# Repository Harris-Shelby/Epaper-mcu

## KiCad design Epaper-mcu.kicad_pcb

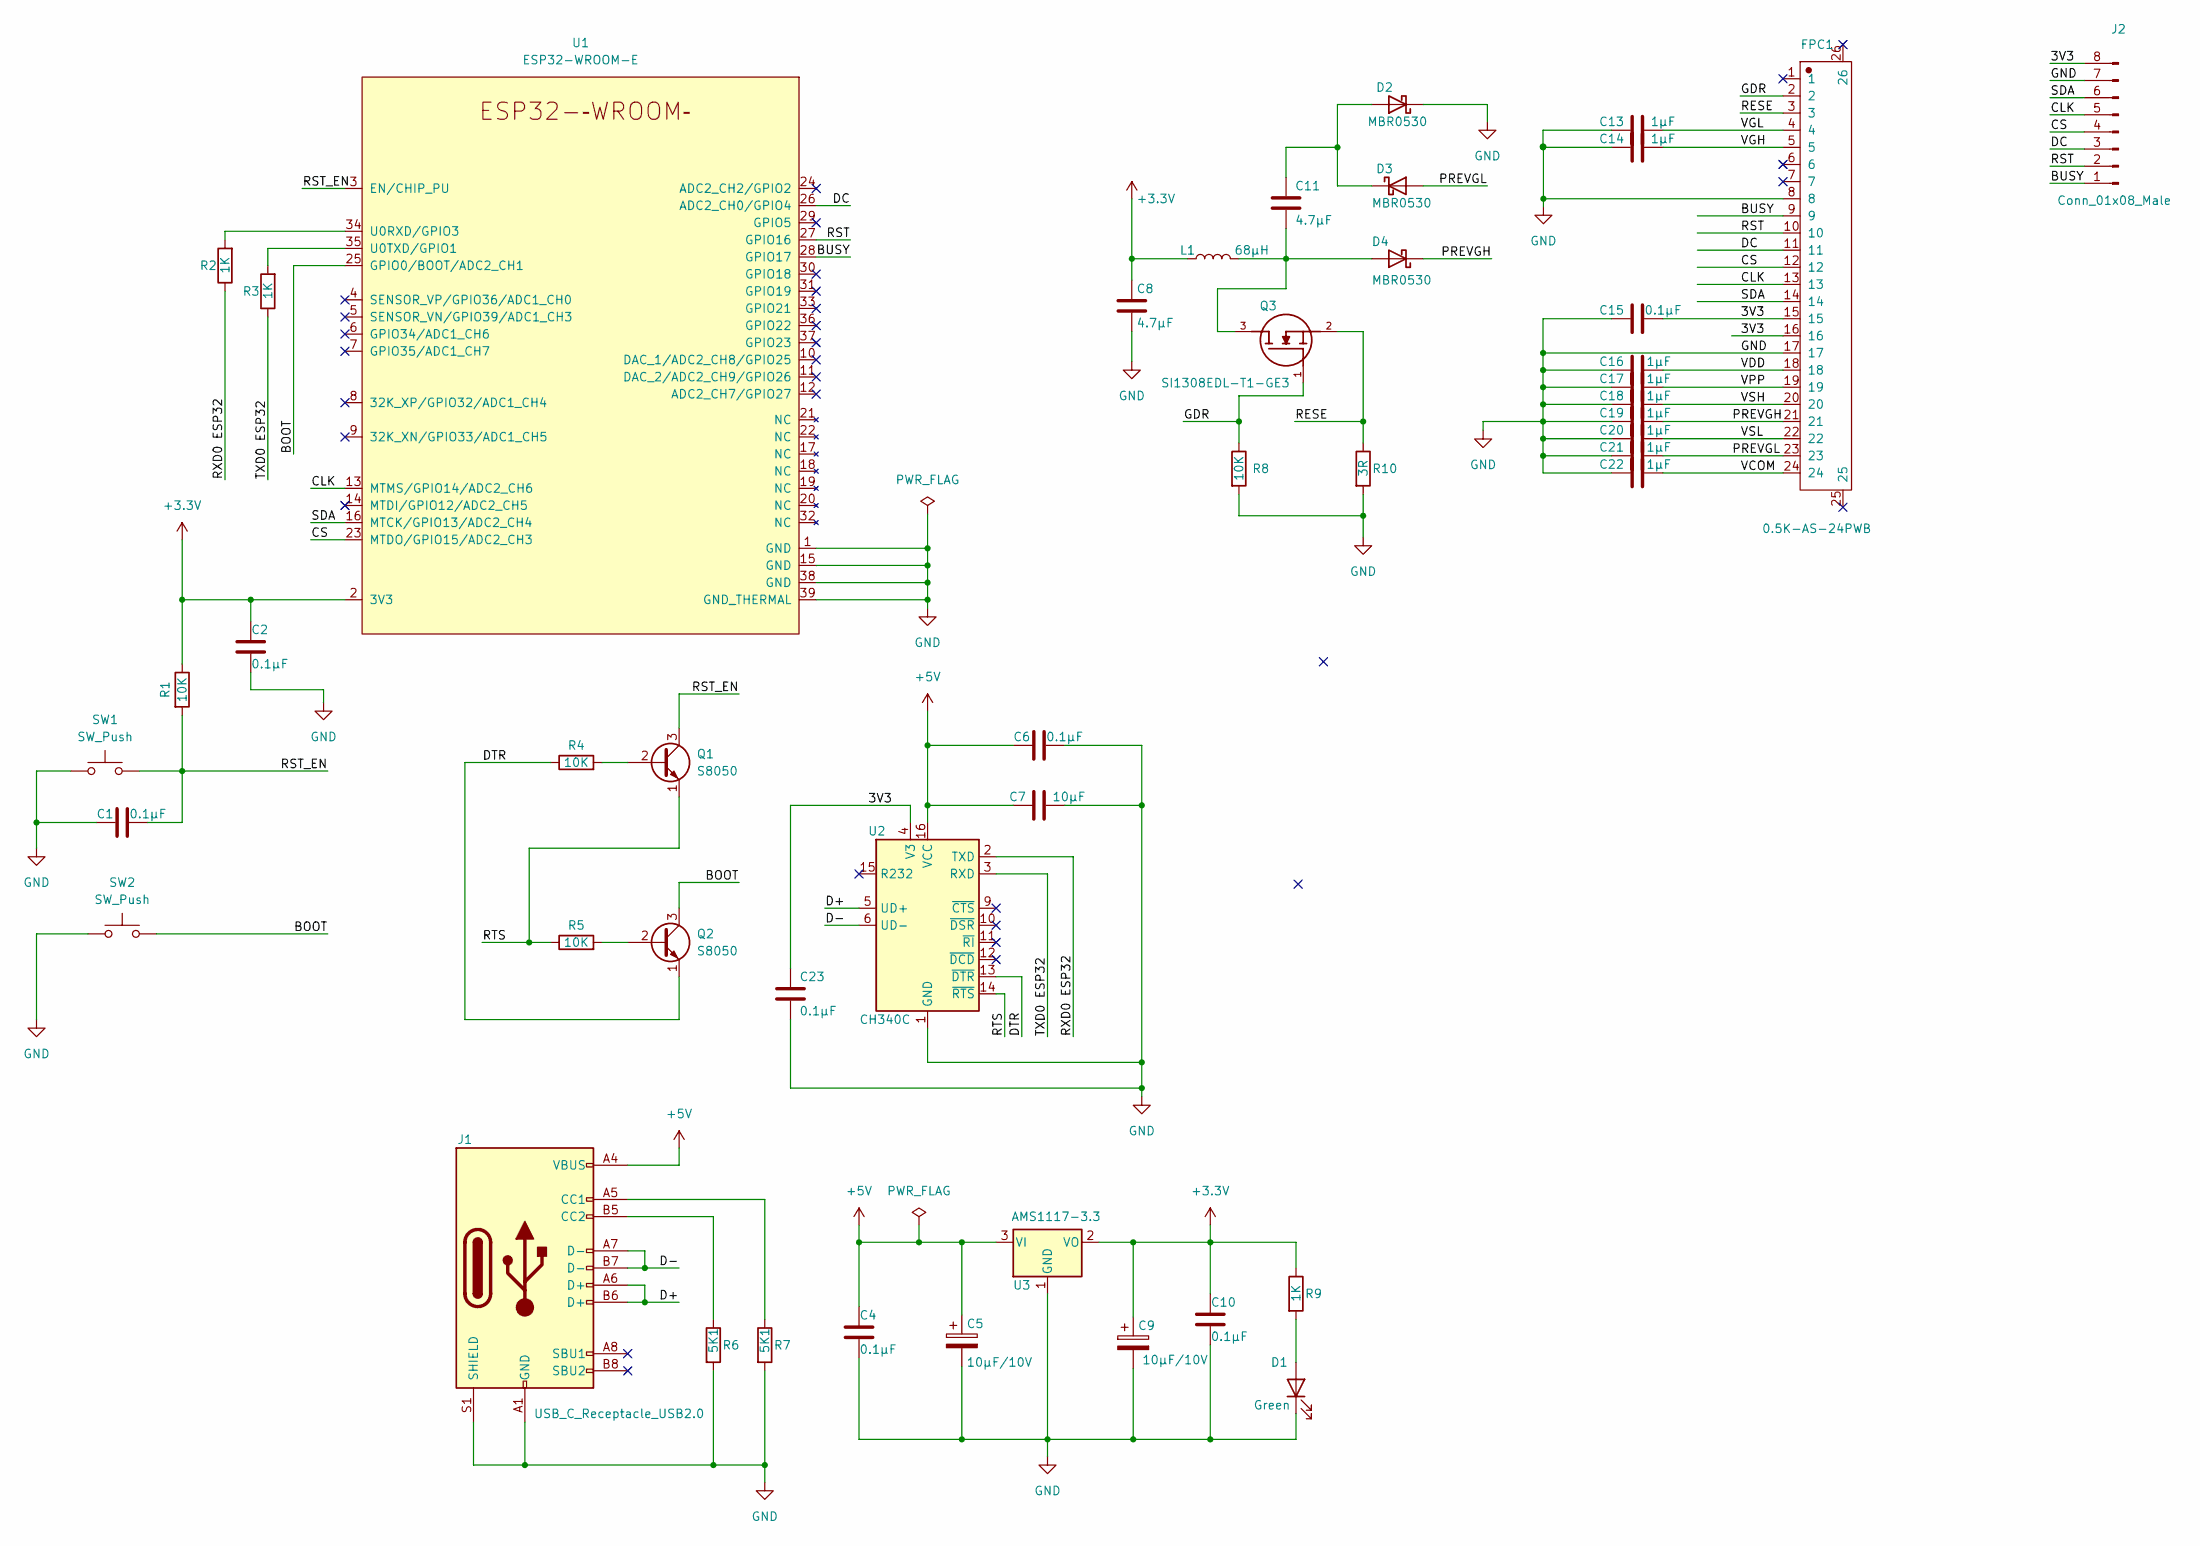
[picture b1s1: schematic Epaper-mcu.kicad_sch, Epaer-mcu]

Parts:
C1, C2, C4, C6, C10: 0.1μF; C_0603_1608Metric
C5, C9: 10μF/10V; C_0603_1608Metric
C7: 10μF; C_0603_1608Metric
C8, C11: 4.7μF; C_0603_1608Metric
C13, C14, C16, C17, C18, C19, C20, C21, C22: 1μF/50V
C15: 0.1μF/50V
C23: 0.1μF
D1: Green; LED_0603_1608Metric
D2, D3, D4: MBR0530; D_SOD-123
FPC1: 0.5K-AS-24PWB; FPC-SMD_24P-P0.50_0.5K-AS-24PWB
J1: USB_C_Receptacle_USB2.0; USB_C_Receptacle_XKB_U262-16XN-4BVC11
J2: Conn_01x08_Male; PinHeader_1x08_P2.54mm_Horizontal
L1: 68μH; IND_VLS3015CX-680M-1
Q1, Q2: S8050; SOT-23
Q3: SI1308EDL-T1-GE3; SOT65P210X110-3N; Mouser_Part_Number 78-SI1308EDL-T1-GE3
R1, R4, R5, R8: 10K; R_0603_1608Metric
R2, R3, R9: 1K; R_0603_1608Metric
R6, R7: 5K1; R_0603_1608Metric
R10: 3R; L_0603_1608Metric
SW1, SW2: SW_Push; SW_SPST_B3U-1000P
U1: ESP32-WROOM-E; ESP32-WROOM-32E
U2: CH340C; SOIC-16_3.9x9.9mm_P1.27mm
U3: AMS1117-3.3; SOT-223-3_TabPin2

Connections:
+3.3V: C2.1, C8.2, C9.1, C10.1, L1.1, R1.1, R9.1, U1.2 (3V3), U3.2 (VO)
+5V: C4.1, C5.1, C6.2, C7.1, J1.A4 (VBUS), J1.A9 (VBUS), J1.B4 (VBUS), J1.B9 (VBUS), U2.16 (VCC), U3.3 (VI)
/3V3: C15.2, C23.1, FPC1.15, FPC1.16, J2.8, U2.4 (V3)
/BOOT: Q2.3 (C), SW2.2, U1.25 (GPIO0/BOOT/ADC2_CH1); also elsewhere on the board
/BUSY: FPC1.9, J2.1, U1.28 (GPIO17)
/CLK: FPC1.13, J2.5, U1.13 (MTMS/GPIO14/ADC2_CH6)
/CS: FPC1.12, J2.4, U1.23 (MTDO/GPIO15/ADC2_CH3)
/D+: J1.A6 (D+), J1.B6 (D+), U2.5 (UD+)
/D-: J1.A7 (D-), J1.B7 (D-), U2.6 (UD-)
/DC: FPC1.11, J2.3, U1.26 (ADC2_CH0/GPIO4)
/DTR: Q2.1 (E), R4.1, U2.13 (~DTR)
/GDR: FPC1.2, Q3.1, R8.1
/PREVGH: C19.2, D4.1 (K), FPC1.21
/PREVGL: C21.2, D3.2 (A), FPC1.23
/RESE: FPC1.3, Q3.2, R10.1
/RST: FPC1.10, J2.2, U1.27 (GPIO16)
/RST_EN: C1.1, Q1.3 (C), R1.2, SW1.2, U1.3 (EN/CHIP_PU); also elsewhere on the board
/RTS: Q1.1 (E), R5.1, U2.14 (~RTS)
/RXD0 ESP32: R2.1, U2.2 (TXD)
/SDA: FPC1.14, J2.6, U1.16 (MTCK/GPIO13/ADC2_CH4)
/TXD0 ESP32: R3.1, U2.3 (RXD)
/VCOM: C22.2, FPC1.24
/VDD: C16.2, FPC1.18
/VGH: C14.2, FPC1.5
/VGL: C13.2, FPC1.4
/VPP: C17.2, FPC1.19
/VSH: C18.2, FPC1.20
/VSL: C20.2, FPC1.22
GND: C1.2, C2.2, C4.2, C5.2, C6.1, C7.2, C8.1, C9.2, C10.2, C15.1, C16.1, C17.1, C18.1, C19.1, C20.1, C21.1, C22.1, C23.2, D1.1 (K), D2.1 (K), FPC1.8, FPC1.17, J1.A1 (GND), J1.A12 (GND), J1.B1 (GND), J1.B12 (GND), J1.S1 (SHIELD), J2.7, R6.2, R7.2, R8.2, R10.2, SW1.1, SW2.1, U1.1 (GND), U1.15 (GND), U1.38 (GND), U1.39 (GND_THERMAL), U2.1 (GND), U3.1 (GND); also elsewhere on the board
unnamed: C11.1, D2.2 (A), D3.1 (K)
unnamed: C11.2, D4.2 (A), L1.2, Q3.3
unnamed: C13.1, C14.1
unnamed 32: D1.2 (A), R9.2; also elsewhere on the board
unnamed: J1.A5 (CC1), R7.1
unnamed: J1.B5 (CC2), R6.1
unnamed: Q1.2 (B), R4.2
unnamed: Q2.2 (B), R5.2
unnamed: R2.2, U1.34 (U0RXD/GPIO3)
unnamed: R3.2, U1.35 (U0TXD/GPIO1)

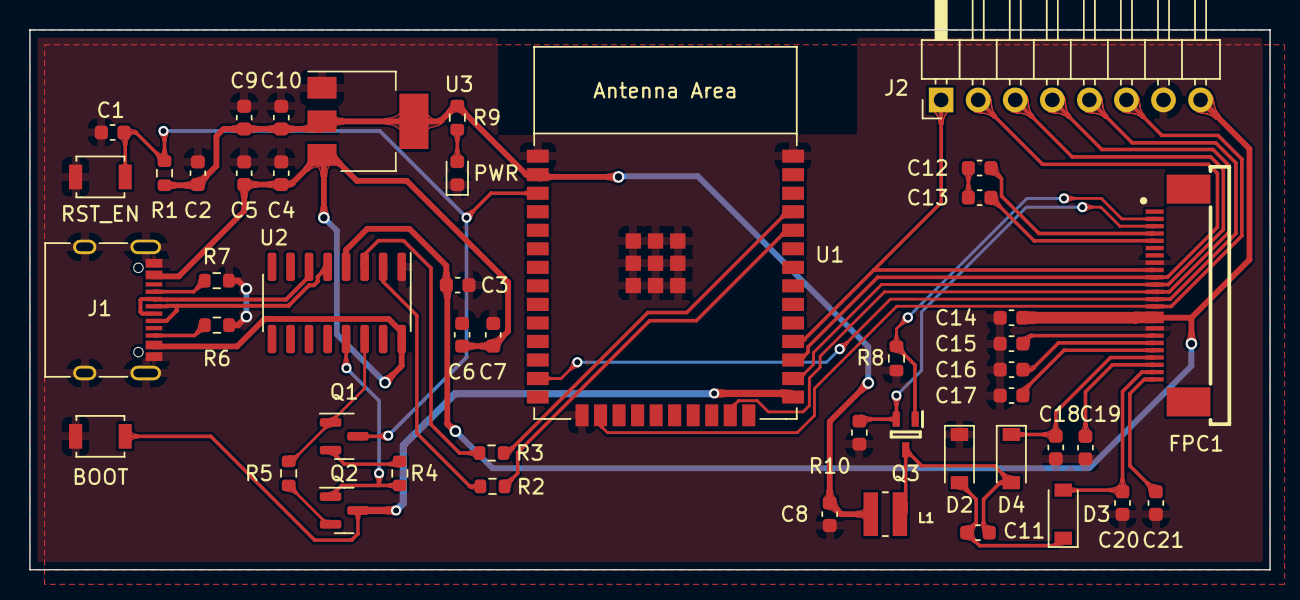
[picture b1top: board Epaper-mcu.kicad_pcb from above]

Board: 2 copper layers, 85.0 x 37.0 mm, 47 parts (0 on the bottom side), 39 nets.

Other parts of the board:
BOOT: SW_Push; SW_SPST_B3U-1000P
PWR: Green; LED_0603_1608Metric
RST_EN: SW_Push; SW_SPST_B3U-1000P

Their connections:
/BOOT: BOOT.2; also elsewhere on the board
/RST_EN: RST_EN.2; also elsewhere on the board
GND: BOOT.1, PWR.1 (K), RST_EN.1; also elsewhere on the board
unnamed 32: PWR.2 (A); also elsewhere on the board

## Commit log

2023-03-14 init kicad project
2023-03-22 Epaper setup
